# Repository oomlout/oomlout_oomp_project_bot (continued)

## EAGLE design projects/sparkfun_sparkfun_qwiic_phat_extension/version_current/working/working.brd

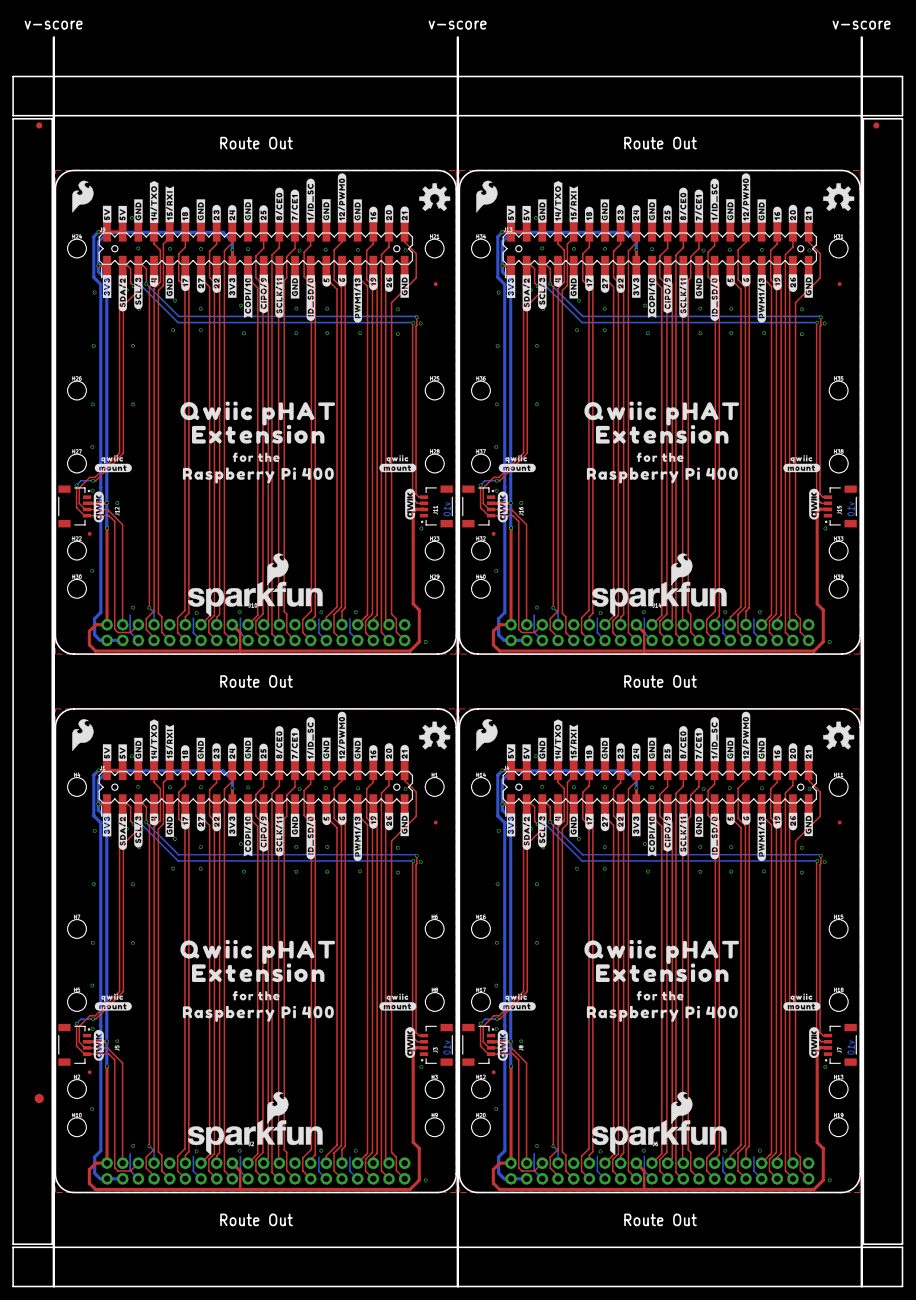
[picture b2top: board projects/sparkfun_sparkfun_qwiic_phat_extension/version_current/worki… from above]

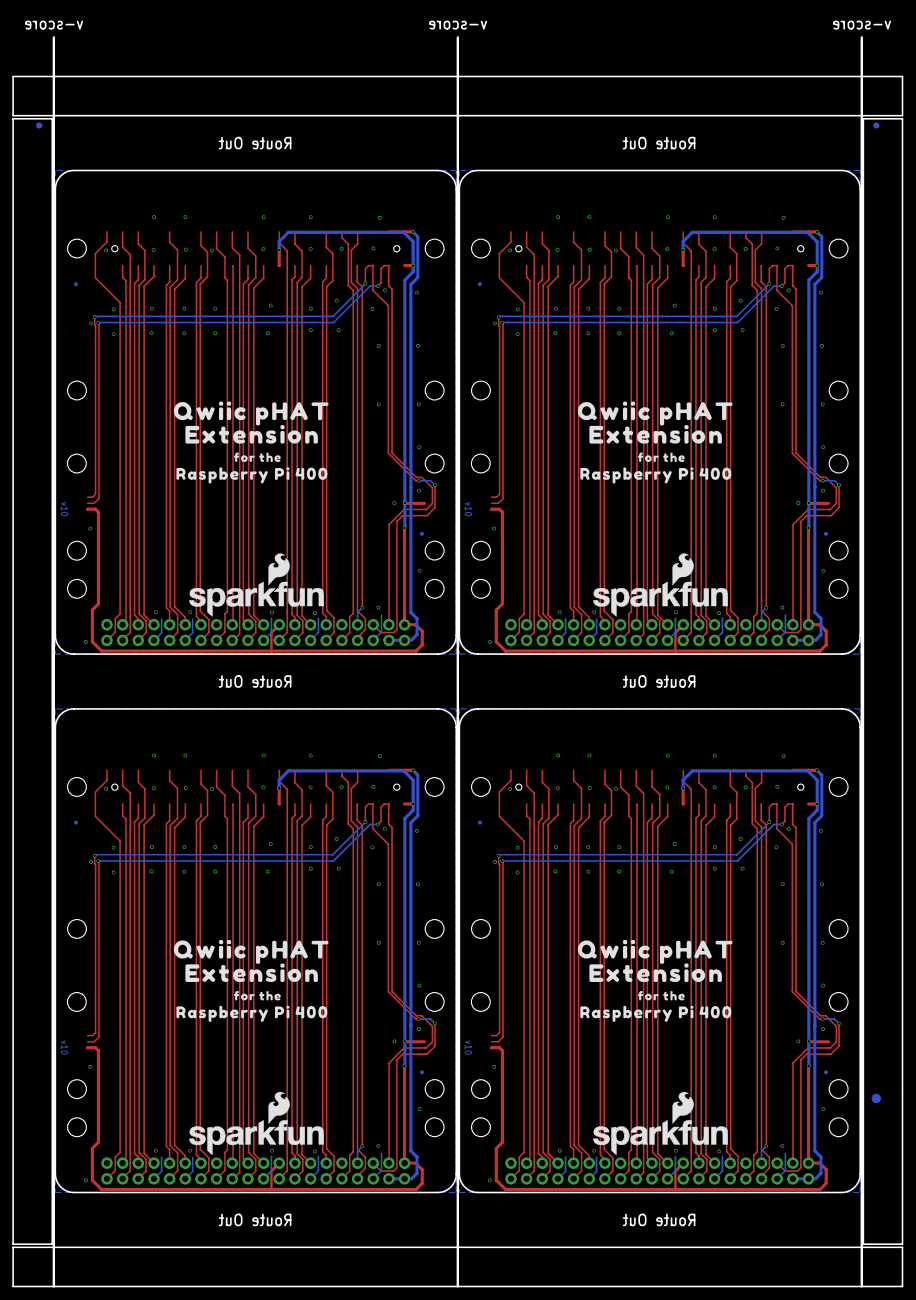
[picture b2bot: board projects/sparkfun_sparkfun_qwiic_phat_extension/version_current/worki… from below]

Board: 2 copper layers, 144.2 x 202.6 mm, 310 parts (31 on the bottom side), 124 nets.

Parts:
E$1, E$2, E$3, E$4: FIDUCIAL-1X2
E$5, E$6: FIDUCIAL-1.5X3
FD1, FD2, FD3, FD4, FD5, FD6, FD7, FD8, FD9, FD10, FD11, FD12, FD13, FD14, FD15, FD16: FIDUCIALUFIDUCIAL; FIDUCIAL-MICRO
H1, H2, H3, H4, H5, H6, H7, H8, H9, H10, H11, H12, H13, H14, H15, H16, H17, H18, H19, H20, H21, H22, H23, H24, H25, H26, H27, H28, H29, H30, H31, H32, H33, H34, H35, H36, H37, H38, H39, H40: STAND-OFFTIGHT; STAND-OFF-TIGHT
J1, J4, J9, J13: RASPBERRYPI-40-PIN-GPIO_SMD_MALE; RASPBERRY_PI_HAT_40_PIN_SMD_MALE
J2, J6, J10, J14: RASPBERRYPI-40-PIN-GPIO_RIGHT_ANGLE; 2X20_RIGHT_ANGLE
J3, J5, J7, J8, J11, J12, J15, J16: QWIIC_RIGHT_ANGLE; JST04_1MM_RA
LOGO1, LOGO4, LOGO6, LOGO9, LOGO11, LOGO14, LOGO16, LOGO19: QWIIC_LOGO_5MM; QWIIC_5MM
LOGO2, LOGO5, LOGO7, LOGO10, LOGO12, LOGO15, LOGO17, LOGO20: SFE_LOGO_NAME_FLAME.2_INCH; SFE_LOGO_NAME_FLAME_.2
LOGO3, LOGO8, LOGO13, LOGO18: OSHW-LOGOM; OSHW-LOGO-M
U$1, U$74, U$138, U$191: #SDA#2#4
U$2, U$77, U$139, U$192: #SCL#3#4
U$3, U$13, U$105, U$106, U$158, U$159, U$211, U$212: FOR_THE40034
U$4, U$5, U$41, U$42, U$107, U$108, U$160, U$161: #3V3#0
U$6, U$43, U$109, U$162: #4#4
U$7, U$44, U$110, U$163: #5#28
U$8, U$9, U$45, U$46, U$111, U$112, U$164, U$165: #5V#28
U$10, U$47, U$113, U$166: #6#28
U$11, U$48, U$114, U$167: #7#CE1#29
U$12, U$49, U$115, U$168: #8#CE0#29
U$14, U$78, U$140, U$193: #SCLK#11#28
U$15, U$79, U$141, U$194: #ID_SD#0#28
U$16, U$50, U$116, U$169: #12#PWM0#29
U$17, U$80, U$142, U$195: #PWM1#13#28
U$18, U$97, U$150, U$203: #14#TXO#29
U$19, U$98, U$151, U$204: #15#RXI#29
U$20, U$53, U$117, U$170: #16#29
U$21, U$54, U$118, U$171: #17#5
U$22, U$55, U$119, U$172: #18#29
U$23, U$56, U$120, U$173: #19#28
U$24, U$57, U$121, U$174: #20#29
U$25, U$58, U$122, U$175: #21#29
U$26, U$59, U$123, U$176: #22#28
U$27, U$60, U$124, U$177: #23#29
U$28, U$61, U$125, U$178: #24#29
U$29, U$62, U$126, U$179: #25#29
U$30, U$63, U$127, U$180: #26#28
U$31, U$64, U$128, U$181: #27#18
U$32, U$33, U$34, U$35, U$36, U$37, U$38, U$39, U$65, U$66, U$67, U$68, U$69, U$70, U$71, U$72, U$129, U$130, U$131, U$132, U$133, U$134, U$135, U$136, U$182, U$183, U$184, U$185, U$186, U$187, U$188, U$189: #GND#28
U$40, U$73, U$137, U$190: #1#ID_SC#29
U$51, U$88, U$144, U$197: #CIPO#9#28
U$52, U$92, U$145, U$198: #COPI#10#28
U$75, U$89, U$99, U$102, U$152, U$155, U$205, U$208: QWIIC_PHAT31
U$76, U$90, U$100, U$103, U$153, U$156, U$206, U$209: EXTENSION32
U$81, U$87, U$143, U$196: SFE_LOGO_FLAME_.2
U$82, U$83, U$93, U$94, U$146, U$147, U$199, U$200: #MOUNT#29
U$84, U$85, U$95, U$96, U$148, U$149, U$201, U$202: QWIIC30
U$86, U$91, U$101, U$104, U$154, U$157, U$207, U$210: RASPBERRY_PI_40033

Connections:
0/ID_SD: J1.27, J2.27
0/ID_SD1: J4.27, J6.27
0/ID_SD2: J9.27, J10.27
0/ID_SD3: J13.27, J14.27
1/ID_SC: J1.28, J2.28
1/ID_SC1: J4.28, J6.28
1/ID_SC2: J9.28, J10.28
1/ID_SC3: J13.28, J14.28
2/SDA: J1.3, J2.3, J3.3, J5.3
2/SDA1: J4.3, J6.3, J7.3, J8.3
2/SDA2: J9.3, J10.3, J11.3, J12.3
2/SDA3: J13.3, J14.3, J15.3, J16.3
3.3V: J1.1, J1.17, J2.1, J2.17, J3.2, J5.2
3.3V1: J4.1, J4.17, J6.1, J6.17, J7.2, J8.2
3.3V2: J9.1, J9.17, J10.1, J10.17, J11.2, J12.2
3.3V3: J13.1, J13.17, J14.1, J14.17, J15.2, J16.2
3/SCL: J1.5, J2.5, J3.4, J5.4
3/SCL1: J4.5, J6.5, J7.4, J8.4
3/SCL2: J9.5, J10.5, J11.4, J12.4
3/SCL3: J13.5, J14.5, J15.4, J16.4
5V: J1.2, J1.4, J2.2, J2.4
5V1: J4.2, J4.4, J6.2, J6.4
5V2: J9.2, J9.4, J10.2, J10.4
5V3: J13.2, J13.4, J14.2, J14.4
7/CE1: J1.26, J2.26
7/CE2: J4.26, J6.26
7/CE3: J9.26, J10.26
7/CE4: J13.26, J14.26
8/CE0: J1.24, J2.24
8/CE1: J4.24, J6.24
8/CE2: J9.24, J10.24
8/CE3: J13.24, J14.24
9/CIPO: J1.21, J2.21
9/CIPO1: J4.21, J6.21
9/CIPO2: J9.21, J10.21
9/CIPO3: J13.21, J14.21
10/COPI: J1.19, J2.19
10/COPI1: J4.19, J6.19
10/COPI2: J9.19, J10.19
10/COPI3: J13.19, J14.19
11/SCLK: J1.23, J2.23
11/SCLK1: J4.23, J6.23
11/SCLK2: J9.23, J10.23
11/SCLK3: J13.23, J14.23
12/PWM0: J1.32, J2.32
12/PWM1: J4.32, J6.32
12/PWM2: J9.32, J10.32
12/PWM3: J13.32, J14.32
13/PWM1: J1.33, J2.33
13/PWM2: J4.33, J6.33
13/PWM3: J9.33, J10.33
13/PWM4: J13.33, J14.33
14/TXO: J1.8, J2.8
14/TXO1: J4.8, J6.8
14/TXO2: J9.8, J10.8
14/TXO3: J13.8, J14.8
15/RXI: J1.10, J2.10
15/RXI1: J4.10, J6.10
15/RXI2: J9.10, J10.10
15/RXI3: J13.10, J14.10
18/PCM_CLK: J1.12, J2.12
18/PCM_CLK1: J4.12, J6.12
18/PCM_CLK2: J9.12, J10.12
18/PCM_CLK3: J13.12, J14.12
19/PCM_FS: J1.35, J2.35
19/PCM_FS1: J4.35, J6.35
19/PCM_FS2: J9.35, J10.35
19/PCM_FS3: J13.35, J14.35
20/PCM_DIN: J1.38, J2.38
20/PCM_DIN1: J4.38, J6.38
20/PCM_DIN2: J9.38, J10.38
20/PCM_DIN3: J13.38, J14.38
21/PCM_DOUT: J1.40, J2.40
21/PCM_DOUT1: J4.40, J6.40
21/PCM_DOUT2: J9.40, J10.40
21/PCM_DOUT3: J13.40, J14.40
GND: J1.6, J1.9, J1.14, J1.20, J1.25, J1.30, J1.34, J1.39, J2.6, J2.9, J2.14, J2.20, J2.25, J2.30, J2.34, J2.39, J3.1, J5.1
GND1: J4.6, J4.9, J4.14, J4.20, J4.25, J4.30, J4.34, J4.39, J6.6, J6.9, J6.14, J6.20, J6.25, J6.30, J6.34, J6.39, J7.1, J8.1
GND2: J9.6, J9.9, J9.14, J9.20, J9.25, J9.30, J9.34, J9.39, J10.6, J10.9, J10.14, J10.20, J10.25, J10.30, J10.34, J10.39, J11.1, J12.1
GND3: J13.6, J13.9, J13.14, J13.20, J13.25, J13.30, J13.34, J13.39, J14.6, J14.9, J14.14, J14.20, J14.25, J14.30, J14.34, J14.39, J15.1, J16.1
GP1: J4.7, J6.7
GP2: J4.29, J6.29
GP3: J4.31, J6.31
GP4: J1.7, J2.7
GP5: J1.29, J2.29
GP6: J1.31, J2.31
GP7: J4.36, J6.36
GP8: J4.11, J6.11
GP9: J4.15, J6.15
GP10: J4.16, J6.16
GP11: J4.18, J6.18
GP12: J4.22, J6.22
GP13: J4.37, J6.37
GP14: J4.13, J6.13
GP15: J9.7, J10.7
GP16: J1.36, J2.36
GP17: J1.11, J2.11
GP18: J9.29, J10.29
GP19: J9.31, J10.31
GP20: J9.36, J10.36
GP21: J9.11, J10.11
GP22: J1.15, J2.15
GP23: J1.16, J2.16
GP24: J1.18, J2.18
GP25: J1.22, J2.22
GP26: J1.37, J2.37
GP27: J1.13, J2.13
GP28: J9.15, J10.15
GP29: J9.16, J10.16
GP30: J9.18, J10.18
GP31: J9.22, J10.22
GP32: J9.37, J10.37
GP33: J9.13, J10.13
GP34: J13.7, J14.7
GP35: J13.29, J14.29
GP36: J13.31, J14.31
GP37: J13.36, J14.36
GP38: J13.11, J14.11
GP39: J13.15, J14.15
GP40: J13.16, J14.16
GP41: J13.18, J14.18
GP42: J13.22, J14.22
GP43: J13.37, J14.37
GP44: J13.13, J14.13

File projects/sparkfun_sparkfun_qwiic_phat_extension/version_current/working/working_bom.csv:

"Id";"Designator";"Footprint";"Quantity";"Designation";"Supplier and ref";
1;"U$168,U$49,U$115,U$12";"#8#CE0#29";4;"";;;
2;"U$181,U$128,U$31,U$64";"#27#18";4;"";;;
3;"U$135,U$37,U$39,U$72,U$134,U$187,U$129,U$130,U$131,U$67,U$69,U$185,U$71,U$136,U$182,U$35,U$32,U$188,U$33,U$66,U$186,U$132,U$189,U$183,U$133,U$184,U$70,U$65,U$36,U$38,U$68,U$34";"#GND#28";32;"";;;
4;"U$192,U$2,U$139,U$77";"#SCL#3#4";4;"";;;
5;"U$173,U$56,U$120,U$23";"#19#28";4;"";;;
6;"U$196,U$81,U$143,U$87";"SFE_LOGO_FLAME_.2";4;"";;;
7;"U$146,U$83,U$200,U$93,U$94,U$147,U$199,U$82";"#MOUNT#29";8;"";;;
8;"U$191,U$138,U$74,U$1";"#SDA#2#4";4;"";;;
9;"U$162,U$109,U$43,U$6";"#4#4";4;"";;;
10;"U$110,U$163,U$44,U$7";"#5#28";4;"";;;
11;"U$105,U$3,U$158,U$211,U$159,U$106,U$212,U$13";"FOR_THE40034";8;"";;;
12;"U$85,U$201,U$96,U$148,U$95,U$149,U$202,U$84";"QWIIC30";8;"";;;
13;"H22,H18,H15,H25,H36,H40,H38,H6,H31,H1,H16,H10,H19,H11,H30,H12,H24,H14,H37,H21,H32,H33,H8,H17,H7,H34,H2,H9,H29,H23,H39,H3,H28,H35,H5,H26,H20,H27,H13,H4";"STAND-OFF-TIGHT";40;"STAND-OFFTIGHT";;;
14;"U$108,U$160,U$161,U$107,U$5,U$42,U$4,U$41";"#3V3#0";8;"";;;
15;"FD2,FD1,FD14,FD6,FD5,FD13,FD10,FD9,FD7,FD3,FD15,FD12,FD8,FD11,FD16,FD4";"FIDUCIAL-MICRO";16;"FIDUCIALUFIDUCIAL";;;
16;"U$86,U$101,U$154,U$207,U$210,U$104,U$91,U$157";"RASPBERRY_PI_40033";8;"";;;
17;"LOGO13,LOGO18,LOGO3,LOGO8";"OSHW-LOGO-M";4;"OSHW-LOGOM";;;
18;"U$153,U$76,U$206,U$100,U$209,U$103,U$90,U$156";"EXTENSION32";8;"";;;
19;"U$204,U$151,U$19,U$98";"#15#RXI#29";4;"";;;
20;"LOGO16,LOGO6,LOGO19,LOGO4,LOGO1,LOGO14,LOGO11,LOGO9";"QWIIC_5MM";8;"QWIIC_LOGO_5MM";;;
21;"U$45,U$46,U$8,U$165,U$112,U$9,U$111,U$164";"#5V#28";8;"";;;
22;"U$17,U$80,U$195,U$142";"#PWM1#13#28";4;"";;;
23;"J7,J3,J11,J12,J5,J8,J15,J16";"JST04_1MM_RA";8;"QWIIC_RIGHT_ANGLE";;;
24;"U$150,U$203,U$18,U$97";"#14#TXO#29";4;"";;;
25;"U$15,U$79,U$141,U$194";"#ID_SD#0#28";4;"";;;
26;"J9,J1,J13,J4";"RASPBERRY_PI_HAT_40_PIN_SMD_MALE";4;"RASPBERRYPI-40-PIN-GPIO_SMD_MALE";;;
27;"U$55,U$22,U$119,U$172";"#18#29";4;"";;;
28;"U$178,U$61,U$125,U$28";"#24#29";4;"";;;
29;"U$170,U$53,U$20,U$117";"#16#29";4;"";;;
30;"U$175,U$122,U$25,U$58";"#21#29";4;"";;;
31;"LOGO7,LOGO12,LOGO17,LOGO2,LOGO20,LOGO15,LOGO10,LOGO5";"SFE_LOGO_NAME_FLAME_.2";8;"SFE_LOGO_NAME_FLAME.2_INCH";;;
32;"U$88,U$144,U$51,U$197";"#CIPO#9#28";4;"";;;
33;"U$57,U$174,U$24,U$121";"#20#29";4;"";;;
34;"U$78,U$193,U$140,U$14";"#SCLK#11#28";4;"";;;
35;"U$137,U$190,U$40,U$73";"#1#ID_SC#29";4;"";;;
36;"U$26,U$123,U$59,U$176";"#22#28";4;"";;;
37;"U$30,U$180,U$63,U$127";"#26#28";4;"";;;
38;"U$47,U$10,U$166,U$113";"#6#28";4;"";;;
39;"U$152,U$205,U$75,U$99,U$102,U$155,U$208,U$89";"QWIIC_PHAT31";8;"";;;
40;"U$124,U$60,U$27,U$177";"#23#29";4;"";;;
41;"U$92,U$198,U$52,U$145";"#COPI#10#28";4;"";;;
42;"U$171,U$21,U$54,U$118";"#17#5";4;"";;;
43;"U$16,U$169,U$116,U$50";"#12#PWM0#29";4;"";;;
44;"U$11,U$48,U$114,U$167";"#7#CE1#29";4;"";;;
45;"U$29,U$179,U$126,U$62";"#25#29";4;"";;;
46;"J14,J10,J2,J6";"2X20_RIGHT_ANGLE";4;"RASPBERRYPI-40-PIN-GPIO_RIGHT_ANGLE";;;
47;"E$5,E$6";"FIDUCIAL-1.5X3";2;"";;;
48;"E$3,E$1,E$4,E$2";"FIDUCIAL-1X2";4;"";;;

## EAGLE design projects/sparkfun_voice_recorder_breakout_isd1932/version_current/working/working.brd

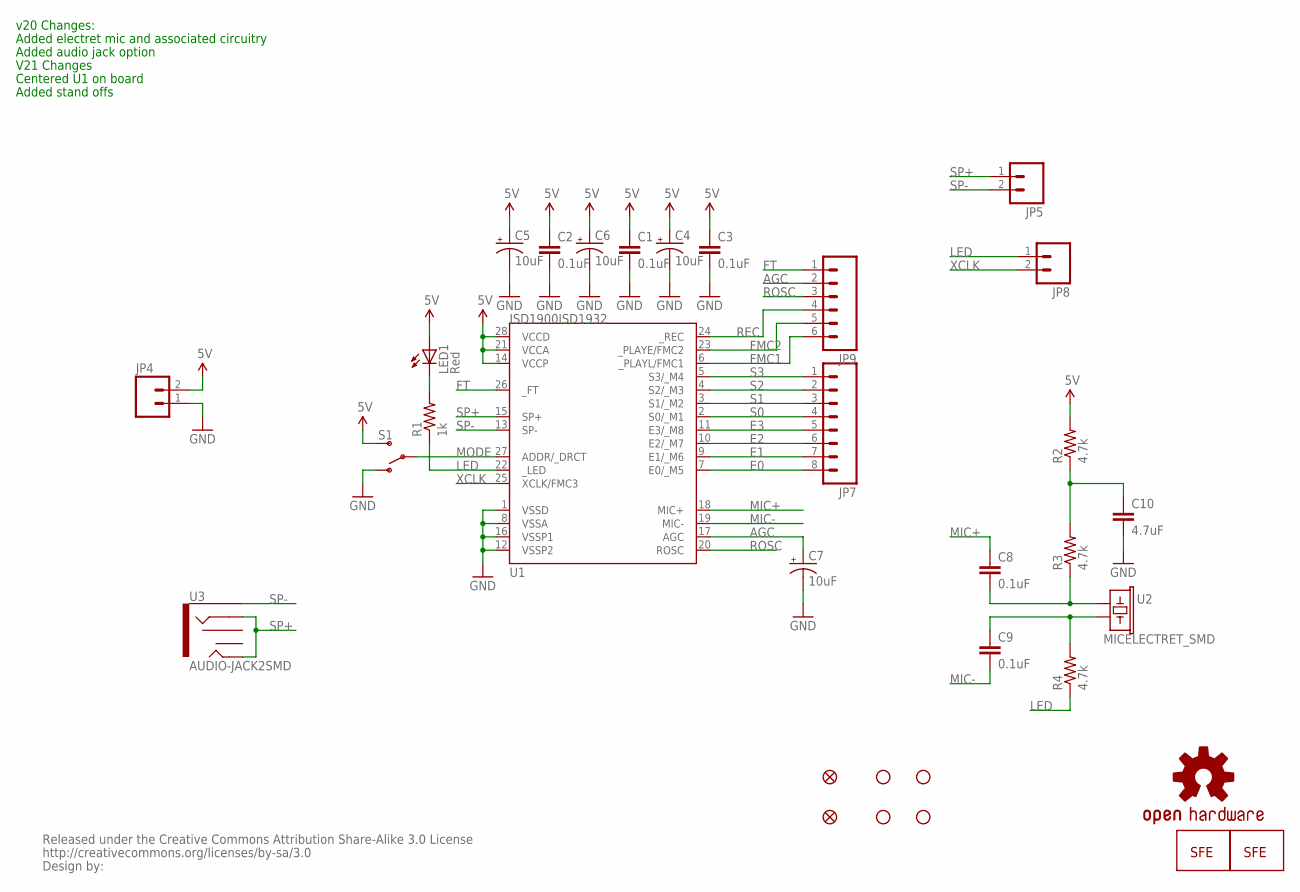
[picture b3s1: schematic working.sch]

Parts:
C1, C2, C3, C8, C9: 0.1uF; 0603-CAP
C4, C5, C6, C7: 10uF; EIA3216
C10: 4.7uF; 0603-CAP
JP1: LOGO-SFENEW; SFE-NEW-WEBLOGO
JP2, JP3: FIDUCIAL1X2; FIDUCIAL-1X2
JP4, JP5, JP8: M02PTH; 1X02
JP6, JP10, JP11, JP12: STAND-OFF
JP7: M08; 1X08
JP9: M06SIP; 1X06
JP13: LOGO-SFENW2; SFE-NEW-WEB
LED1: Red; LED-0603
R1: 1k; 0603-RES
R2, R3, R4: 4.7k; 0603-RES
S1: SWITCH-SPSTSMD; AYZ0202
U1: ISD1900ISD1932; SO-28W
U2: MICELECTRET_SMD; MIC_ELECTRET_SMD
U3: AUDIO-JACK2SMD; AUDIO-JACK-3.5MM-SMD
U$10: CREATIVE_COMMONS
U$14: OSHW-LOGOL; OSHW-LOGO-L

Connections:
5V: C1.1, C2.1, C3.1, C4.A (+), C5.A (+), C6.A (+), JP4.2, LED1.A, R2.2, S1.3 (S), U1.14 (VCCP), U1.21 (VCCA), U1.28 (VCCD)
AGC: C7.A (+), JP9.2, U1.17 (AGC)
E0: JP7.8, U1.7 (E0/_M5)
E1: JP7.7, U1.9 (E1/_M6)
E2: JP7.6, U1.10 (E2/_M7)
E3: JP7.5, U1.11 (E3/_M8)
FMC1: JP9.6, U1.6 (_PLAYL/FMC1)
FMC2: JP9.5, U1.23 (_PLAYE/FMC2)
FT: JP9.1, U1.26 (_FT)
GND: C1.2, C2.2, C3.2, C4.C (-), C5.C (-), C6.C (-), C7.C (-), C10.2, JP4.1, S1.1 (O), U1.1 (VSSD), U1.8 (VSSA), U1.12 (VSSP2), U1.16 (VSSP1)
LED: JP8.1, R1.1, R4.1, U1.22 (_LED)
MIC+: C8.1, U1.18 (MIC+)
MIC-: C9.2, U1.19 (MIC-)
MODE: S1.2, U1.27 (ADDR/_DRCT)
unnamed: LED1.C, R1.2
unnamed: C8.2, R3.1, U2.1
unnamed: C9.1, R4.2, U2.2
unnamed: C10.1, R2.1, R3.2
REC: JP9.4, U1.24 (_REC)
ROSC: JP9.3, U1.20 (ROSC)
S0: JP7.4, U1.2 (S0/_M1)
S1: JP7.3, U1.3 (S1/_M2)
S2: JP7.2, U1.4 (S2/_M3)
S3: JP7.1, U1.5 (S3/_M4)
SP+: JP5.1, U1.15 (SP+), U3.RING, U3.TIP
SP-: JP5.2, U1.13 (SP-), U3.SLEEVE
XCLK: JP8.2, U1.25 (XCLK/FMC3)

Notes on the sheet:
v20 Changes:
Added electret mic and associated circuitry
Added audio jack option
V21 Changes
Centered U1 on board
Added stand offs

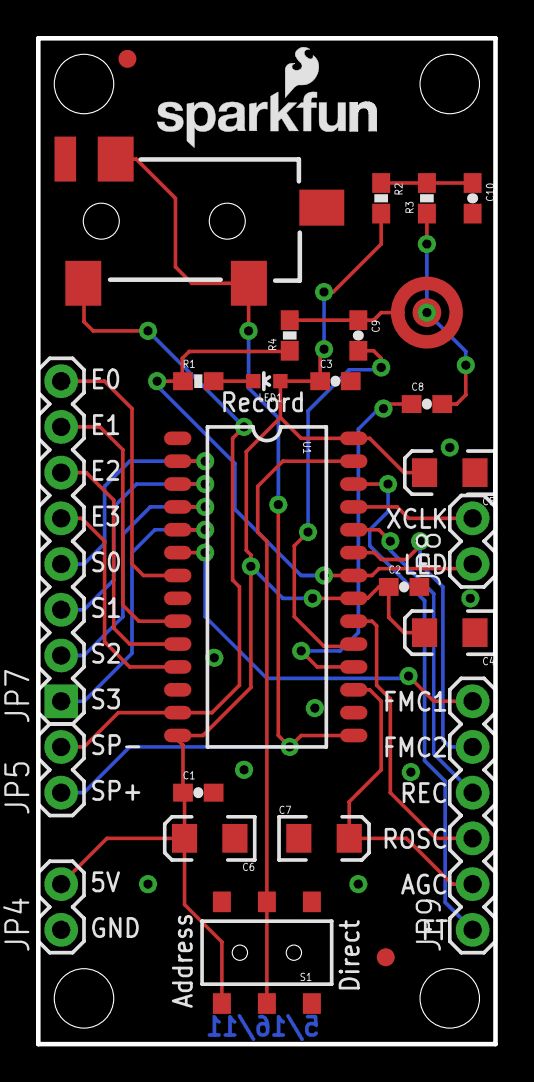
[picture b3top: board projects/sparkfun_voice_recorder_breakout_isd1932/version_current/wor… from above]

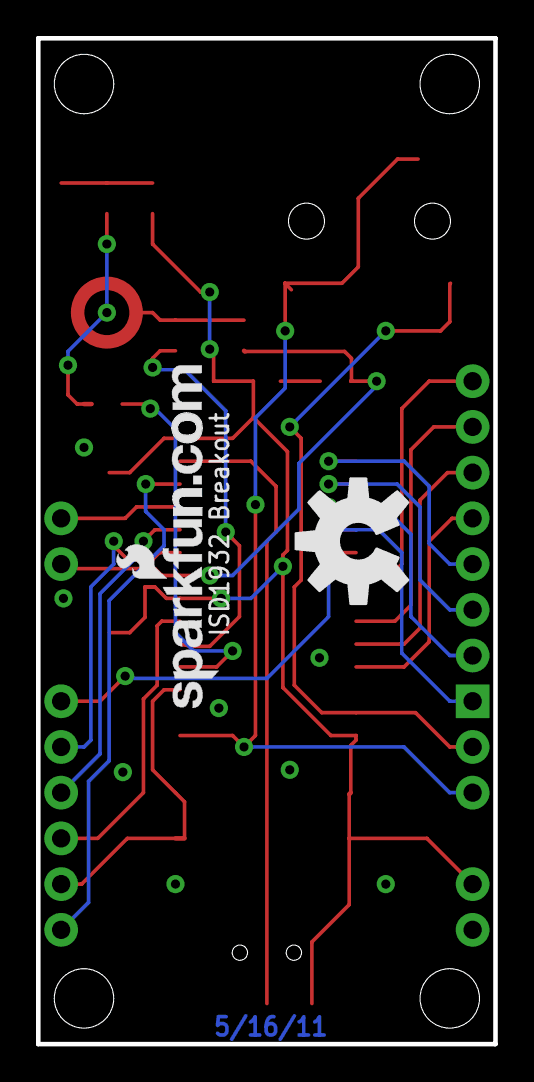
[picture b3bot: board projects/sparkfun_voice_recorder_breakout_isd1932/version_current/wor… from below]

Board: 2 copper layers, 25.4 x 55.9 mm, 35 parts (2 on the bottom side), 27 nets.

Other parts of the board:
U$13: SFE-LOGO-FLAME

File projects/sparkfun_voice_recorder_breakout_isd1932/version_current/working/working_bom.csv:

"Id";"Designator";"Footprint";"Quantity";"Designation";"Supplier and ref";
1;"S1";"AYZ0202";1;"";;;
2;"C10";"0603-CAP";1;"4.7uF";;;
3;"C8,C3,C9,C1,C2";"0603-CAP";5;"0.1uF";;;
4;"JP5,JP8,JP4";"1X02";3;"";;;
5;"R3,R4,R2";"0603-RES";3;"4.7k";;;
6;"LED1";"LED-0603";1;"Red";;;
7;"JP11,JP10,JP6,JP12";"STAND-OFF";4;"STAND-OFF";;;
8;"JP13";"SFE-NEW-WEB";1;"LOGO-SFENW2";;;
9;"U$13";"SFE-LOGO-FLAME";1;"";;;
10;"JP7";"1X08";1;"";;;
11;"C5,C6,C4,C7";"EIA3216";4;"10uF";;;
12;"U2";"MIC_ELECTRET_SMD";1;"MICELECTRET_SMD";;;
13;"R1";"0603-RES";1;"1k";;;
14;"JP9";"1X06";1;"";;;
15;"U1";"SO-28W";1;"ISD1900ISD1932";;;
16;"JP2,JP3";"FIDUCIAL-1X2";2;"FIDUCIAL1X2";;;
17;"U$10";"CREATIVE_COMMONS";1;"CREATIVE_COMMONS";;;
18;"U3";"AUDIO-JACK-3.5MM-SMD";1;"AUDIO-JACK2SMD";;;
19;"U$14";"OSHW-LOGO-L";1;"OSHW-LOGOL";;;
20;"JP1";"SFE-NEW-WEBLOGO";1;"LOGO-SFENEW";;;
